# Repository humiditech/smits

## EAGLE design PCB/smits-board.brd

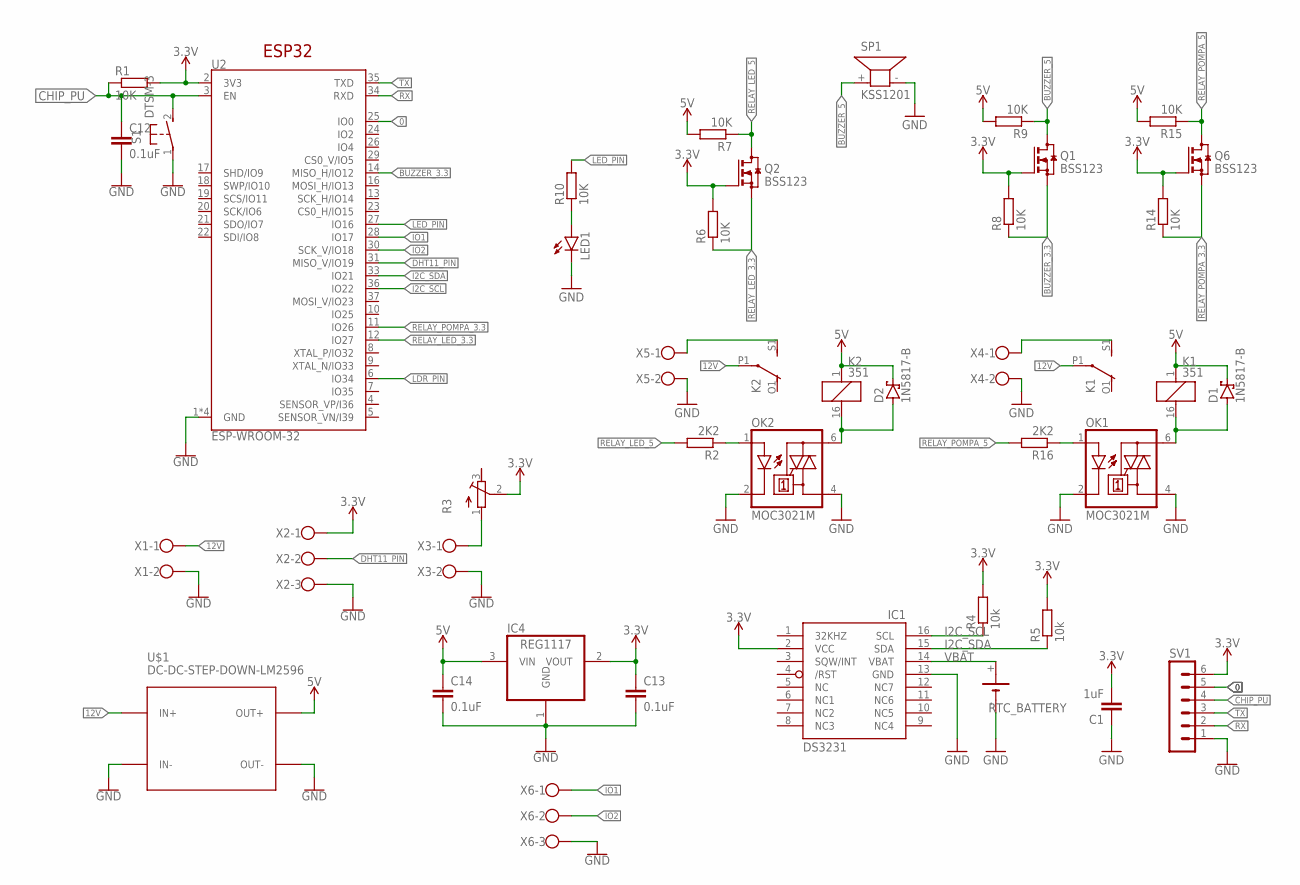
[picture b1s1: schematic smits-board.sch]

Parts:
C1: 1uF; C0805
C12, C13, C14: 0.1uF; C0805
D1, D2: 1N5817-B; DO41-7.6
IC1: DS3231/SO; SO16W
IC4: REG1117; SOT223
K1, K2: 351
LED1: LEDCHIP-LED0805; CHIP-LED0805
OK1, OK2: MOC3021M; DIL06
Q1, Q2, Q6: BSS123; SOT23
R1, R6, R7, R8, R9, R10, R14, R15: 10K; R0805
R2, R16: 2K2; R0805
R3: R-TRIMM64W; RTRIM64W
R4, R5: 10k; R0805
RTC_BATTERY: CH291-1220LF
S1: DTSM-3
SP1: KSS1201
SV1: MA06-1
U2: ESP-WROOM-32
U$1: DC-DC-STEP-DOWN-LM2596
X1, X3, X4, X5: W237-102
X2, X6: W237-103

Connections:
0: SV1.5, U2.25 (IO0)
12V: K1.P1, K2.P1, U$1.IN+, X1.1
BUZZER_3.3: Q1.2 (S), R8.1, U2.14 (MISO_H/IO12)
BUZZER_5: Q1.3 (D), R9.1, SP1.+ (1)
CHIP_PU: C12.1, R1.1, S1.2, SV1.4, U2.3 (EN)
DHT11_PIN: U2.31 (MISO_V/IO19), X2.2
GND: C1.1, C12.2, C13.2, C14.2, IC1.13 (GND), IC4.1 (GND), LED1.C, OK1.2 (C), OK1.4 (A1), OK2.2 (C), OK2.4 (A1), RTC_BATTERY.-, S1.1, SP1.- (2), SV1.1, U2.1 (GND), U2.15 (GND), U2.38 (GND), U2.GND, U$1.IN-, U$1.OUT-, X1.2, X2.3, X3.2, X4.2, X5.2, X6.3
I2C_SCL: IC1.16 (SCL), R4.1, U2.36 (IO22)
I2C_SDA: IC1.15 (SDA), R5.1, U2.33 (IO21)
IO1: U2.28 (IO17), X6.1
IO2: U2.30 (SCK_V/IO18), X6.2
LDR_PIN: U2.6 (IO34)
LED_PIN: R10.2, U2.27 (IO16)
unnamed: R3.1 (A), X3.1
unnamed: D1.A, K1.16 (2), OK1.6 (A2)
unnamed: OK1.1 (A), R16.1
unnamed: D2.A, K2.16 (2), OK2.6 (A2)
unnamed: LED1.A, R10.1
unnamed: K1.S1 (S), X4.1
unnamed: OK2.1 (A), R2.1
unnamed: K2.S1 (S), X5.1
RELAY_LED_3.3: Q2.2 (S), R6.1, U2.12 (IO27)
RELAY_LED_5: Q2.3 (D), R2.2, R7.1
RELAY_POMPA_3.3: Q6.2 (S), R14.1, U2.11 (IO26)
RELAY_POMPA_5: Q6.3 (D), R15.1, R16.2
RX: SV1.2, U2.34 (RXD)
TX: SV1.3, U2.35 (TXD)
VBAT: IC1.14 (VBAT), RTC_BATTERY.+
VCC_1: C1.2, C13.1, IC1.2 (VCC), IC4.2 (VOUT), Q1.1 (G), Q2.1 (G), Q6.1 (G), R1.2, R3.2 (S), R4.2, R5.2, R6.2, R8.2, R14.2, SV1.6, U2.2 (3V3), X2.1
VCC_2: C14.1, D1.C, D2.C, IC4.3 (VIN), K1.1, K2.1, R7.2, R9.2, R15.2, U$1.OUT+

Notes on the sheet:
ESP32

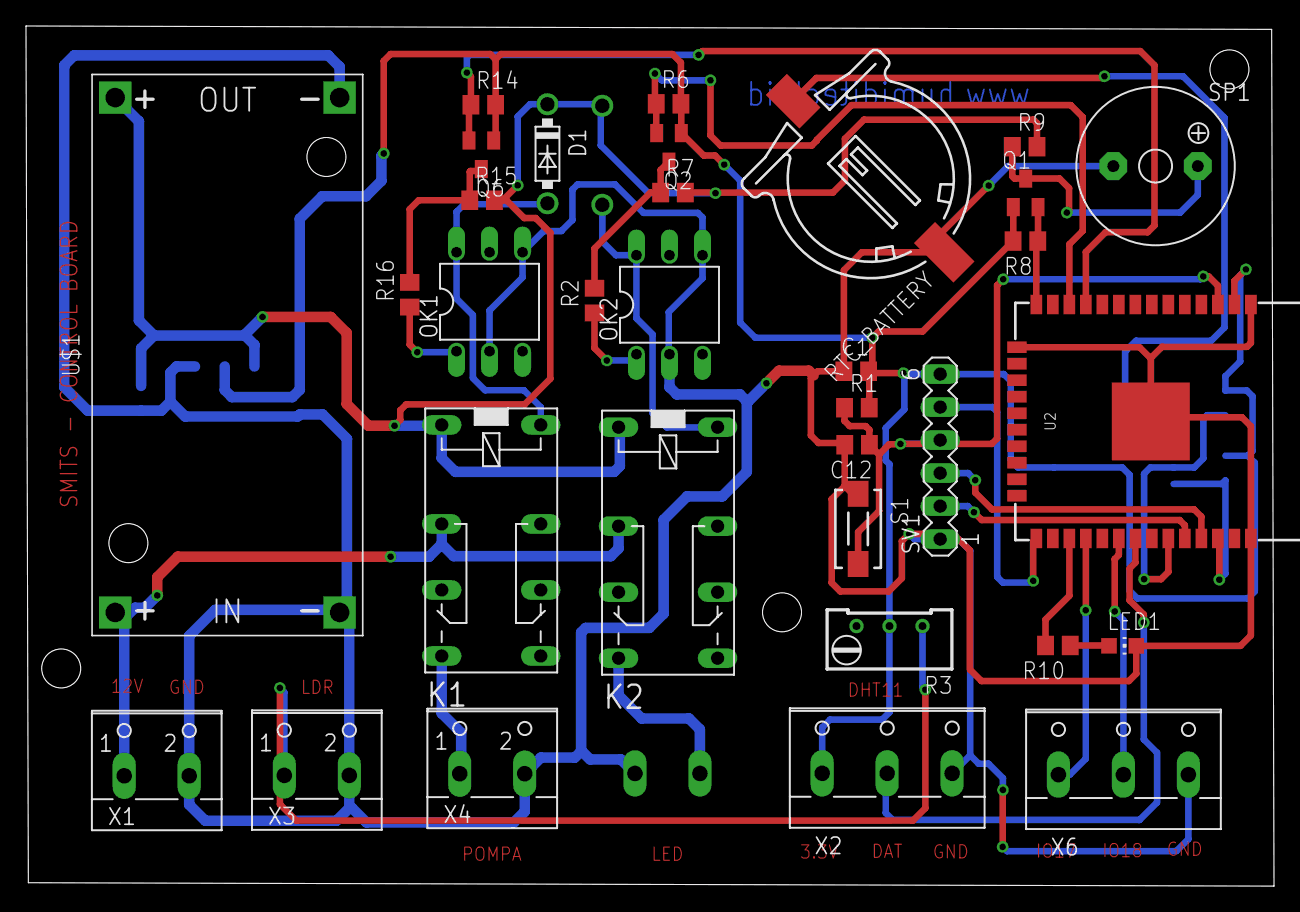
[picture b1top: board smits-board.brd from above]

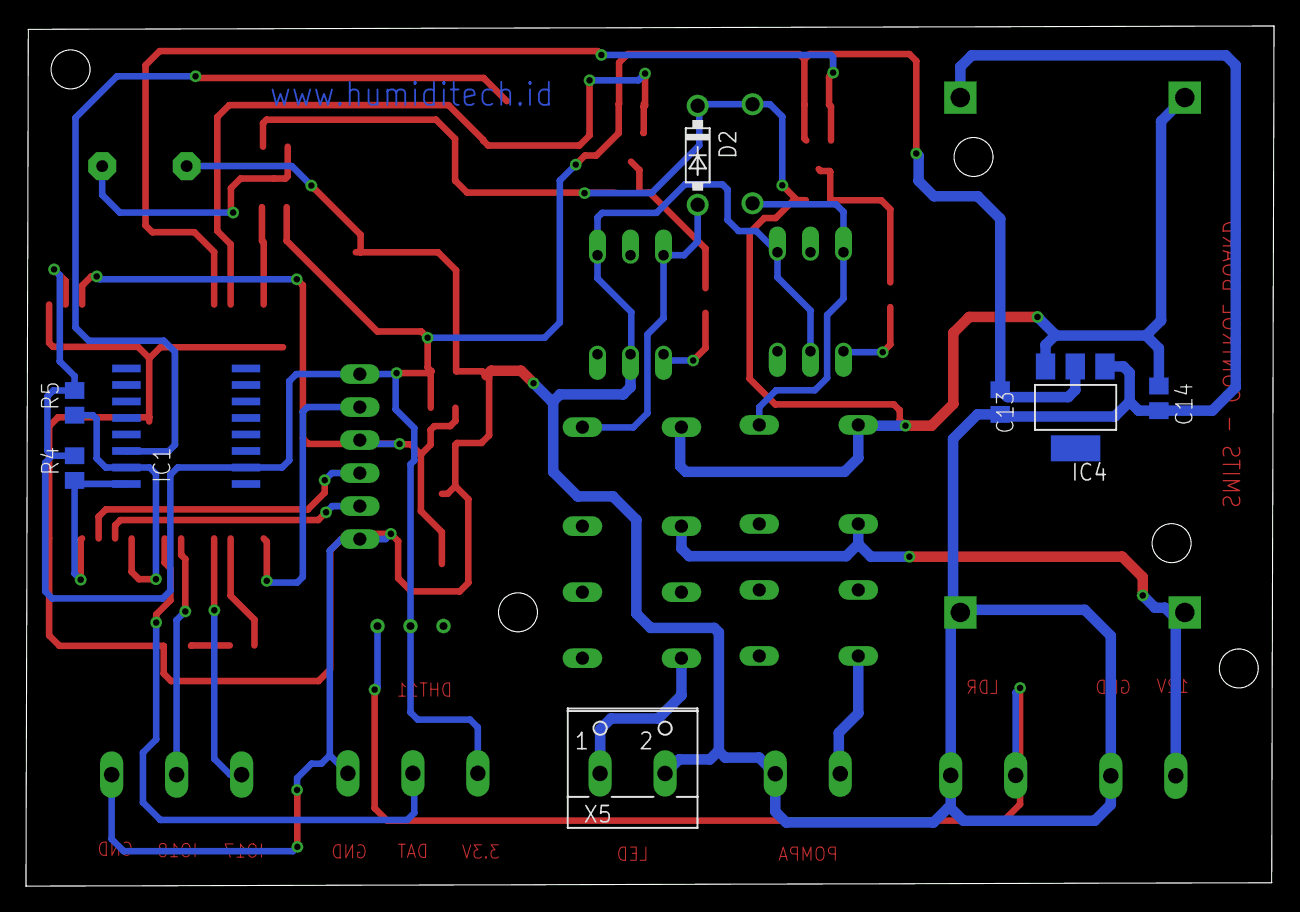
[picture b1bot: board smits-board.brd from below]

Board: 2 copper layers, 96.0 x 66.2 mm, 41 parts (8 on the bottom side), 29 nets.

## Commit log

2021-06-27 add pcb file
2021-07-04 add firmware file
2021-07-04 update main code
2021-07-18 update firmware
2021-08-09 update firmware code

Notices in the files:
parts and their libraries:
SparkFun-RF: Licensing: Creative Commons ShareAlike 4.0 International - https://creativecommons.org/licenses/by-sa/4.0
diy-modules: Released under the Creative Commons Attribution 4.0 International License: http://creativecommons.org/licenses/by/4.0
